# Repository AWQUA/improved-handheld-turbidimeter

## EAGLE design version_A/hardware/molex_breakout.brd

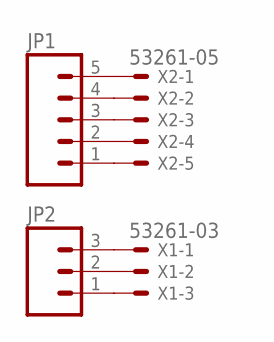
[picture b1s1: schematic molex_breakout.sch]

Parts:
JP1: M05PTH; 1X05
JP2: M03PTH; 1X03
X1: 53261-03
X2: 53261-05

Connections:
unnamed: JP2.3, X1.1
unnamed: JP2.2, X1.2
unnamed: JP2.1, X1.3
unnamed: JP1.5, X2.1
unnamed: JP1.4, X2.2
unnamed: JP1.3, X2.3
unnamed: JP1.2, X2.4
unnamed: JP1.1, X2.5

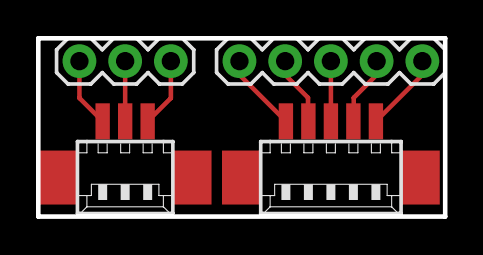
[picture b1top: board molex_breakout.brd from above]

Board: 2 copper layers, 22.6 x 9.9 mm, 4 parts (0 on the bottom side), 8 nets.

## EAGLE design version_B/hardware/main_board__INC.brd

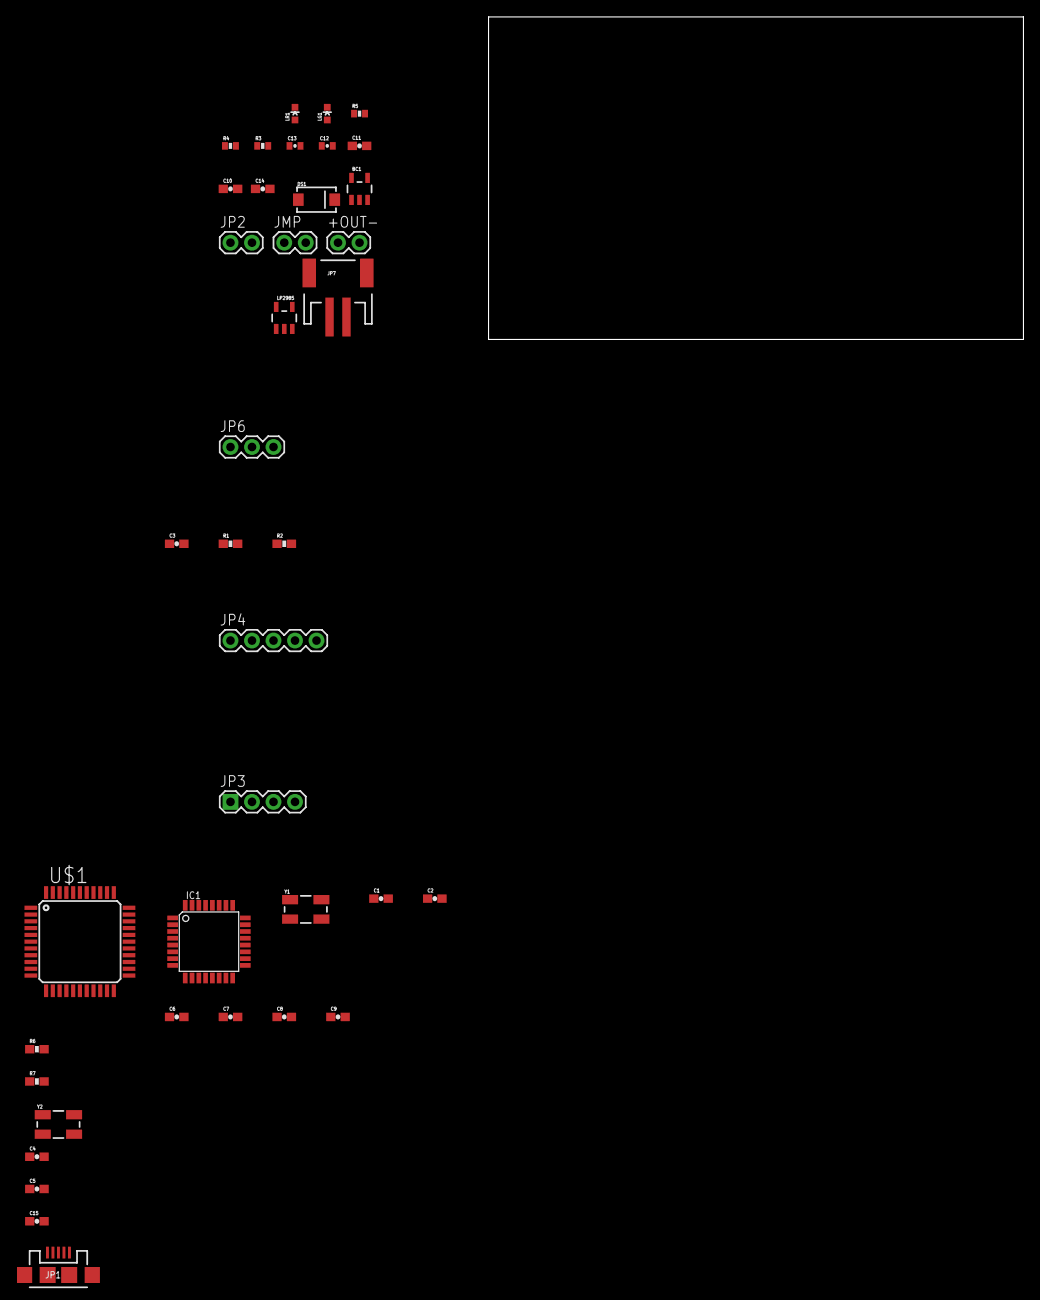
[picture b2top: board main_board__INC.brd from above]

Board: 2 copper layers, 63.2 x 38.1 mm, 39 parts (0 on the bottom side), 29 nets, no tracks yet.

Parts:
+OUT-: 1X02
BC1: MCP73831; SOT23-5
C1, C2, C4, C5: 18p; 0603-CAP
C3, C6, C7, C8, C15: 100n; 0603-CAP
C9, C10: 1uF; 0603-CAP
C11: 2.2uF; 0603-CAP
C12, C13: 4.7uF; 0402-CAP
C14: 10nF (OPT); 0603-CAP
DS1: MBRA140; SMA-DIODE
IC1: MEGA8-AI; TQFP32-08
JMP: 1X02
JP1: USB-MICROB
JP2: 1X02
JP3: 1X04
JP4: 1X05
JP6: 1X03
JP7: LiPo Battery; JST-2-SMD
LG1: GREEN; LED-0603
LR1: RED; LED-0603
R1: 33.2k; 0603-RES
R2: 14k; 0603-RES
R3: 2K; 0402-RES
R4, R5: 330; 0402-RES
R6, R7: 22; 0603-RES
U$1: ATMEGA32U4-AU; TQFP44
VR1: LP2985
Y1, Y2: CRYSTAL-SMD-5X3

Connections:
AREF: C7.1, IC1.20
BTN1: IC1.2, JP3.4
BTN2: IC1.9, JP3.3
BTN3: IC1.10, JP3.2
D+: JP1.D+, R7.2
D-: JP1.D-, R6.2
GND: +OUT-.2, BC1.2, C1.1, C2.1, C3.1, C4.1, C5.1, C6.2, C7.2, C8.2, C9.2, C10.2, C11.2, C12.2, C13.2, C14.2, C15.2, IC1.3, IC1.5, IC1.21, JMP.1, JP1.GND, JP1.MT1, JP1.MT2, JP2.1, JP3.1, JP4.2, JP6.1, JP7.1, LG1.C, R2.1, R3.2, U$1.15, U$1.23, U$1.35, U$1.43, VR1.2
unnamed: C14.1, VR1.4
unnamed: LG1.A, R5.2
unnamed: LR1.A, R4.1
unnamed: +OUT-.1, C11.1, VR1.5
unnamed: DS1.A, JP2.2
unnamed: R6.1, U$1.3
unnamed: R7.1, U$1.4
unnamed: C15.1, U$1.42
unnamed: C4.2, U$1.17, Y2.3
unnamed: C5.2, U$1.16, Y2.1
PROG: BC1.5, R3.1
Q1: C2.2, IC1.8, Y1.1
Q2: C1.2, IC1.7, Y1.3
RST: IC1.29, JP4.5
RX: IC1.30, JP4.3
STAT: BC1.1, LR1.C, R5.1
TEMP: IC1.24, JP6.2
TX: IC1.31, JP4.4
VBUS: JP1.VBUS, U$1.7
VCC: BC1.3, C3.2, C6.1, C8.1, C9.1, C10.1, C13.1, IC1.4, IC1.6, IC1.18, JMP.2, JP4.1, JP6.3, JP7.2, R1.1, VR1.1, VR1.3
VIN: BC1.4, C12.1, DS1.C, R4.2
VOLT: IC1.25, R1.2, R2.2

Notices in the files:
parts and their libraries:
SparkFun-Connectors: Licensing: Creative Commons ShareAlike 4.0 International - https://creativecommons.org/licenses/by-sa/4.0
SparkFun-Resistors: Licensing: CC v3.0 Share-Alike You are welcome to use this library for commercial purposes.
